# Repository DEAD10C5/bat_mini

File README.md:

# Bat Badge 2018  

## Serial

You can make a serial connection to the badge using a USB to TTL serial cable. 

For example: 
[USB to TTL Serial Cable](https://www.adafruit.com/product/954)

- Green wire: Connect to serial port, right side looking at back. 
- White wire: Connect to serial port, left side looking at back.
- Black wire: Connect to Battery port, negative (-) port. 
- Red/Orange wire: Do not connect! This is +5V but the board is at +3V. 

## Programming 

We used an Arduino UNO as an ISP to program the attiny84 chip on the badge. 

[Set up the programming environment](http://highlowtech.org/?p=1695)

We did a "6 way" header similar to the one described at the link below. 

[About ISP headers](http://www.batsocks.co.uk/readme/isp_headers.htm)

## Chip Information

ATMEL ATTINY84 / ARDUINO pinout

````
//

//                      +-\/-+

//                VCC 1|      |14 GND

//       `  (D 0) PB0 2|      |13 AREF (D10)

//          (D 1) PB1 3|      |12 PA1 (D9) 

//                PB3 4|      |11 PA2 (D 8) 

// PWM INT0 (D 2) PB2 5|      |10 PA3 (D 7) 

//      PWM (D 3) PA7 6|      |9 PA4(D 6) 

//      PWM (D 4) PA6 7|      |8 PA5(D 5) PWM

//                      +----+

IDE Attiny84 Physical Pin  Usage
  0      PA0           13  Button
  1      PA1           12  Heart
  2      PA2           11  RGB LED Data Pin
  3      PA3           10  Serial TX
  4      PA4            9
  5      PA5            8  Left Eye
  6      PA6            7  Right Eye
  7      PA7            6
  8      PB2            5
  9      PB1            3  Serial RX 
 10      PB0            2     
```

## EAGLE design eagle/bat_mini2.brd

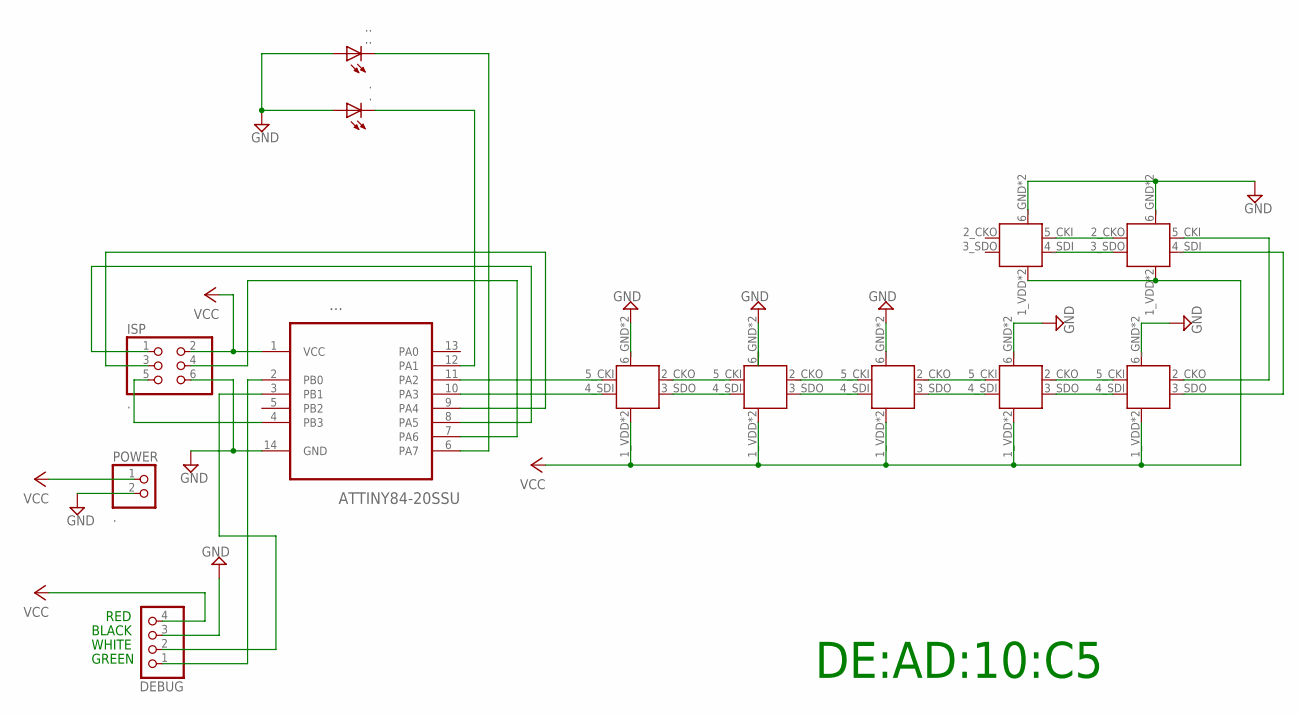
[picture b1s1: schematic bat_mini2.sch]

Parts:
.: .; CHIP-LED0805
..: ..; CHIP-LED0805
...: ATTINY84-20SSU; SOIC127P600X175-14N
DEBUG: PINHD-1X4; 1X04
EYE1, EYE2: APA102; APA102-2020
ISP: .; 2X03
POWER: .; 1X02
U$4, U$5, U$6, U$7, U$8: APA102; APA102-2020

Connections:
GND: ..A, ...A, ....14 (GND), DEBUG.3, EYE1.6_GND (GND), EYE1.GNDPAD (GND), EYE2.6_GND (GND), EYE2.GNDPAD (GND), ISP.6, POWER.2, U$4.6_GND (GND), U$4.GNDPAD (GND), U$5.6_GND (GND), U$5.GNDPAD (GND), U$6.6_GND (GND), U$6.GNDPAD (GND), U$7.6_GND (GND), U$7.GNDPAD (GND), U$8.6_GND (GND), U$8.GNDPAD (GND)
unnamed: ....2 (PB0), DEBUG.1
unnamed: ....8 (PA5), ISP.1
unnamed: ....7 (PA6), ISP.4
unnamed: ....9 (PA4), ISP.3
unnamed: ....4 (PB3), ISP.5
unnamed: ..C, ....12 (PA1)
unnamed: ...C, ....6 (PA7)
unnamed: ....11 (PA2), EYE1.5_CKI (CKI)
unnamed: ....10 (PA3), EYE1.4_SDI (SDI)
unnamed: EYE1.3_SDO (SDO), EYE2.4_SDI (SDI)
unnamed: EYE1.2_CKO (CKO), EYE2.5_CKI (CKI)
unnamed: EYE2.3_SDO (SDO), U$4.4_SDI (SDI)
unnamed: EYE2.2_CKO (CKO), U$4.5_CKI (CKI)
unnamed: ....3 (PB1), DEBUG.2
unnamed: U$4.3_SDO (SDO), U$5.4_SDI (SDI)
unnamed: U$4.2_CKO (CKO), U$5.5_CKI (CKI)
unnamed: U$5.3_SDO (SDO), U$6.4_SDI (SDI)
unnamed: U$5.2_CKO (CKO), U$6.5_CKI (CKI)
unnamed: U$6.2_CKO (CKO), U$7.5_CKI (CKI)
unnamed: U$6.3_SDO (SDO), U$7.4_SDI (SDI)
unnamed: U$7.3_SDO (SDO), U$8.4_SDI (SDI)
unnamed: U$7.2_CKO (CKO), U$8.5_CKI (CKI)
VCC: ....1 (VCC), DEBUG.4, EYE1.1_VDD (VCC), EYE1.VDDPAD (VCC), EYE2.1_VDD (VCC), EYE2.VDDPAD (VCC), ISP.2, POWER.1, U$4.1_VDD (VCC), U$4.VDDPAD (VCC), U$5.1_VDD (VCC), U$5.VDDPAD (VCC), U$6.1_VDD (VCC), U$6.VDDPAD (VCC), U$7.1_VDD (VCC), U$7.VDDPAD (VCC), U$8.1_VDD (VCC), U$8.VDDPAD (VCC)

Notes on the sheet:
RED
BLACK
WHITE
GREEN
DE:AD:10:C5

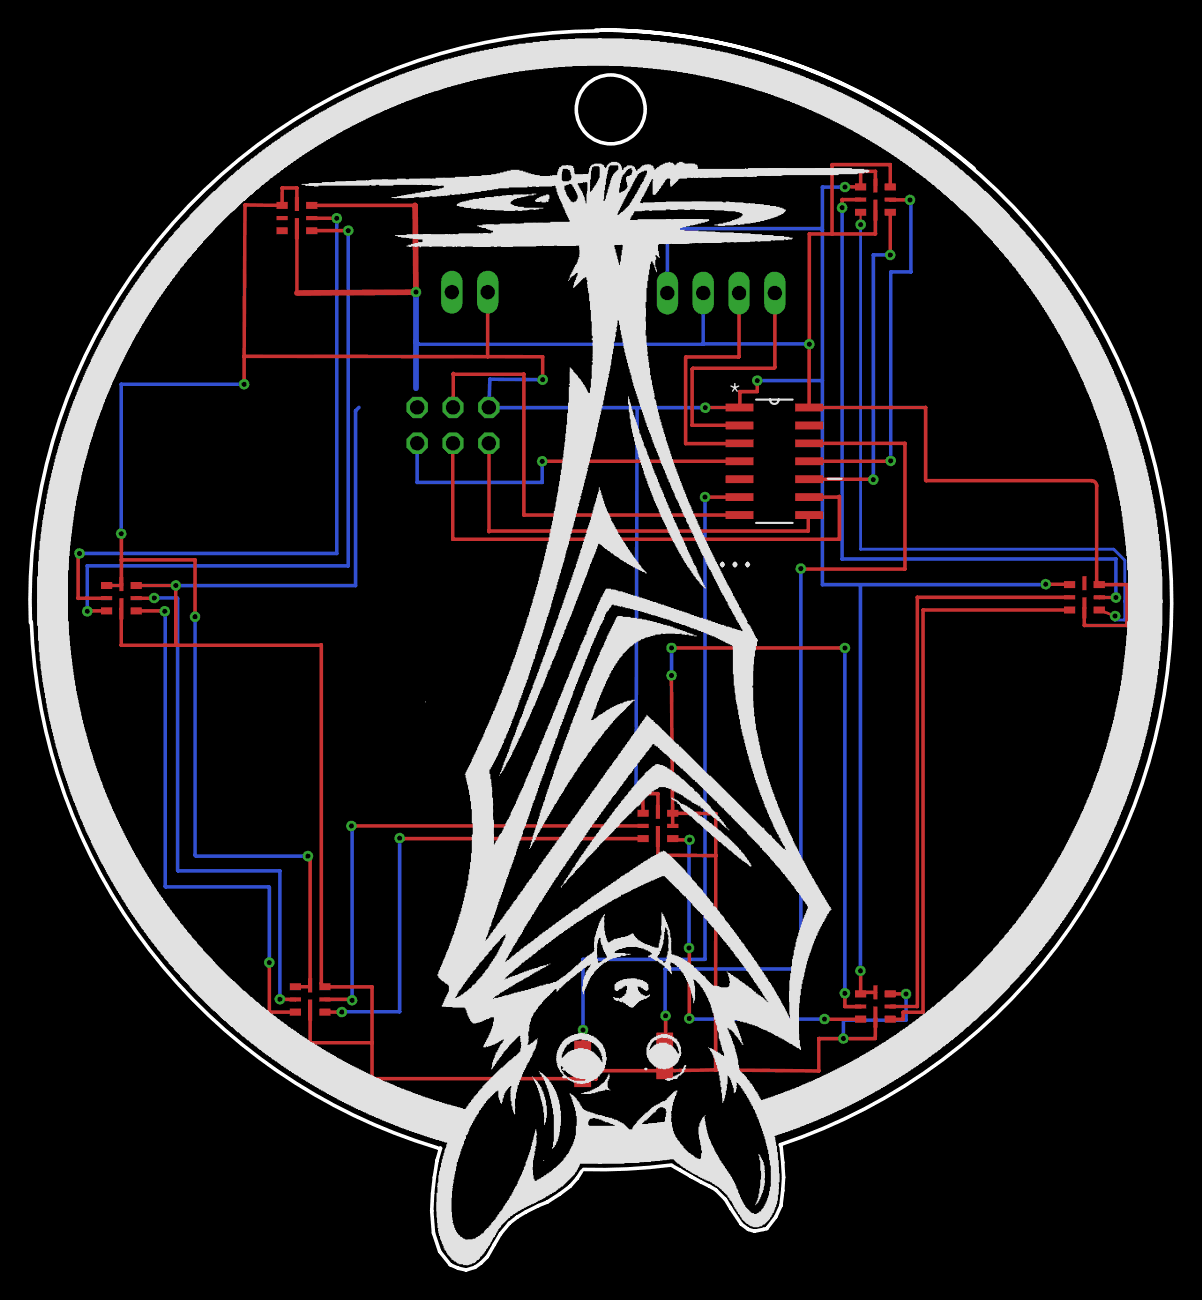
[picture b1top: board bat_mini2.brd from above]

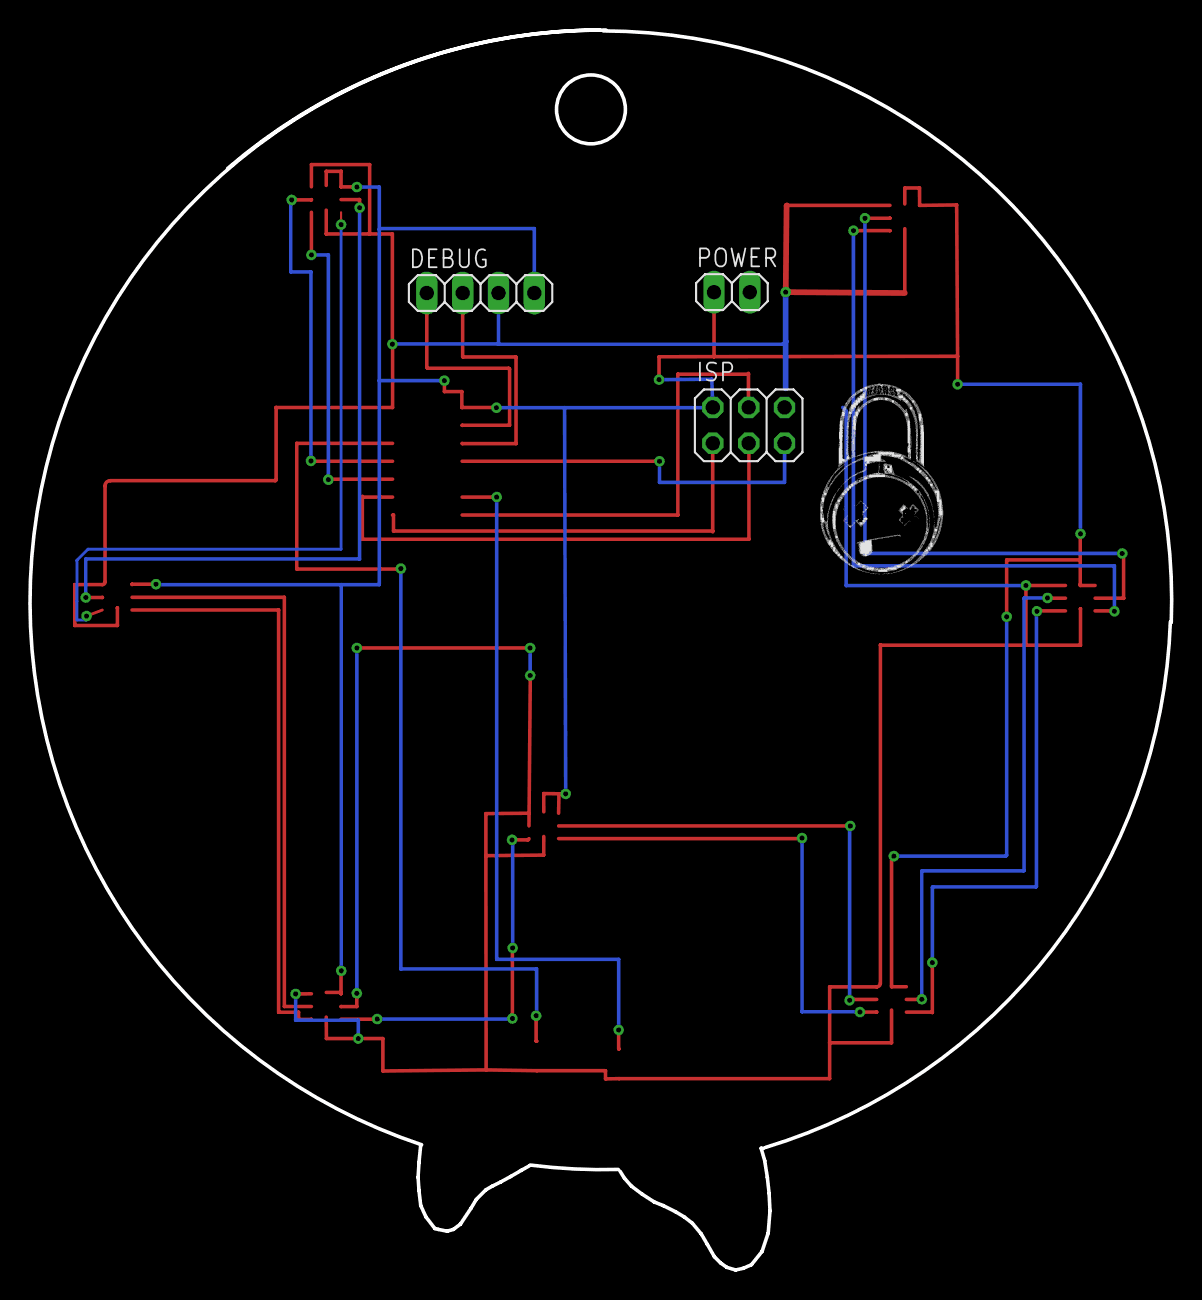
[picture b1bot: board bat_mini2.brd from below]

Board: 2 copper layers, 80.9 x 87.9 mm, 13 parts (3 on the bottom side), 24 nets.

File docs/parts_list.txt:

Partlist

Exported from bat_mini1.brd at 4/3/18 9:11 PM

EAGLE Version 8.7.1 Copyright (c) 1988-2018 Autodesk, Inc.

Assembly variant: 

Part     Value          Package             Library                       Position (mm)         Orientation

.        .              CHIP-LED0805        led                           (47.0625 17.5)        R0
..       ..             CHIP-LED0805        led                           (41.25 16.9375)       R0
DEBUG                   1X02                pinhead                       (51.0625 71.5625)     MR0
EYE1     APA102         APA102-2020         pimoroni-optoelectronics      (62 78.1875)          R0
EYE2     APA102         APA102-2020         pimoroni-optoelectronics      (76.8125 50)          R0
ISP      .              2X03                pinhead                       (32.0625 62.1875)     MR0
POWER    .              1X02                pinhead                       (33.25 71.625)        MR0
U$4      APA102         APA102-2020         pimoroni-optoelectronics      (62 21)               R0
U$5      APA102         APA102-2020         pimoroni-optoelectronics      (45.0625 44.4375)     R0
U$6      APA102         APA102-2020         pimoroni-optoelectronics      (21.9375 21.5)        R0
U$7      APA102         APA102-2020         pimoroni-optoelectronics      (8.5625 49.9375)      R0
U$8      APA102         APA102-2020         pimoroni-optoelectronics      (21 76.875)           R0
U1       ATTINY84-20SSU SOIC127P600X175-14N Atmel_By_element14_Batch_1-00 (54.835 59.64)        R0

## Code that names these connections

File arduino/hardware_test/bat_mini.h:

/*!
   @file bat_mini.h
    ____  _____      _    ____    _  ___     ____ ____
   |  _ \| ____|_   / \  |  _ \ _/ |/ _ \ _ / ___| ___|
   | | | |  _| (_) / _ \ | | | (_) | | | (_) |   |___ \
   | |_| | |___ _ / ___ \| |_| |_| | |_| |_| |___ ___) |
   |____/|_____(_)_/   \_\____/(_)_|\___/(_)\____|____/


   Author : @p0lr_ @mzbat @theDevilsVoice @dead10c5
   Date   : July 4, 2018
   Version: 0.1





                    ATMEL ATTINY84 / ARDUINO

                             +-\/-+
                       VCC  1|    |14  GND
               (D  0)  PB0  2|    |13  AREF (D 10)
               (D  1)  PB1  3|    |12  PA1  (D  9)
                       PB3  4|    |11  PA2  (D  8)
    PWM  INT0  (D  2)  PB2  5|    |10  PA3  (D  7)
    PWM        (D  3)  PA7  6|    |9   PA4  (D  6)
    PWM        (D  4)  PA6  7|    |8   PA5  (D  5)        PWM
                             +----+


*/
#ifndef BAT_H
#define BAT_H
#define VERSION "0.1"

// Defines for LED pulse code
#define BRIGHT    31    //max led intensity (1-500)
#define INHALE    1250    //Inhalation time in milliseconds.
#define PULSE     INHALE*1000/BRIGHT
#define REST      100    //Rest Between Inhalations.

#include <Arduino.h>
#include <APA102.h>

// pins'n'stuff
const uint8_t dataPin    = PA2;
const uint8_t clockPin   = PA3;
const uint8_t heart      = PA7;
const uint8_t left_eye   = PB2;
const uint8_t right_eye  = 0;
const uint8_t button     = 1;
const uint16_t ledCount  = 6;
const uint8_t brightness = 10;


class MyBat {
  public:
    int buttonState;         // variable for reading the pushbutton status
    uint8_t led_pattern_cur;
    
    rgb_color hsvToRgb(uint16_t, uint8_t, uint8_t);
};

#endif

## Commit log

2018-04-07 alpha
2018-04-22 post proto updates
2018-05-05 coin cells & fix routing
2018-06-03 checkpoint
2018-07-04 checkpoint brd 7
2018-07-04 updated hardware test code
2018-07-10 final pcb
2018-08-02 release 1.0
2018-08-04 final tweaks for release 1.0
2018-09-06 grrcon 2018
2018-09-06 testing travis CI
2018-09-06 updated sch, brd, and gerbers
2018-09-06 test CI
2018-09-06 testint CI
2018-09-08 change derby boards
2018-09-08 change no unset
2018-09-08 set HOME
2018-09-08 test
2018-09-08 testing
2018-09-09 test travis
2018-09-09 update travis
2018-09-09 update serial
2018-09-16 cleaup
2018-09-17 typoes
2018-09-20 test new light pattern
2018-09-20 fix version
2018-10-06 experimental sleep for power saving
2018-10-07 change to the adc enable/disable function, not using sbi/cbi
2018-10-10 moved sleep to 64 and added delay 100 back
    sleep might be non blocking, unsure.
2018-10-14 testing pwr save
2018-11-15 test coverity
2018-11-15 add coverity shield
2018-11-23 disable coverity scan
